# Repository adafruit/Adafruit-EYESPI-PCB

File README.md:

## Adafruit EYESPI Breakout Board PCB

<a href="http://www.adafruit.com/products/5613"><br/>
Click here to purchase one from the Adafruit shop</a>

PCB files for the Adafruit EYESPI Breakout Board. 

Format is EagleCAD schematic and board layout
* https://www.adafruit.com/product/5613

### Description

Our most recent display breakouts have come with a new feature: an 18-pin "EYE SPI" standard FPC connector with flip-top connector. This is intended to be a sort-of "STEMMA QT for displays" - a way to quickly connect and extend display wiring that uses a lot of SPI pins. In this case we need a lot of SPI pins, and we want to be able to use long distances so we go with an 18-pin 0.5mm pitch FPC.

Now you can connect to the displays, but what goes on the other side of the FPC? Here is one possibility - a simple breakout board that brings all the GPIO to 0.1" spaced header, for breadboarding usage. Each pin usage is labeled, and for most display purposes you only need the left half of the display for power and SPI connectivity.

Don't forget you'll also want an 18-pin EYESPI FPC cable.

### License

Adafruit invests time and resources providing this open source design, please support Adafruit and open-source hardware by purchasing products from [Adafruit](https://www.adafruit.com)!

Designed by Limor Fried/Ladyada for Adafruit Industries.

Creative Commons Attribution/Share-Alike, all text above must be included in any redistribution. 
See license.txt for additional details.

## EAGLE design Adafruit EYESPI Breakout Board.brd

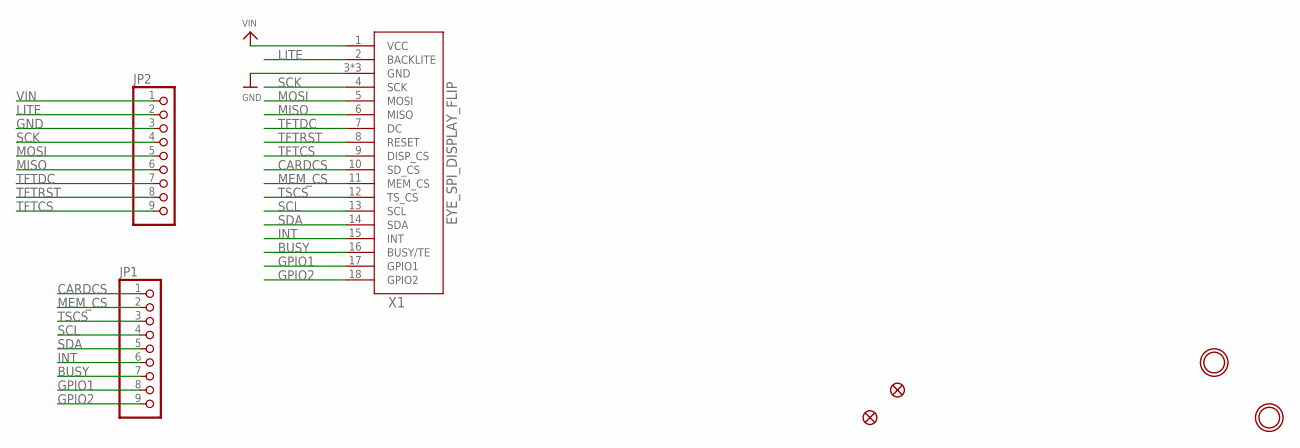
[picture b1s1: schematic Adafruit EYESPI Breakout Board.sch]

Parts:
JP1, JP2: HEADER-1X970MIL; 1X09_ROUND_70
U$4, U$5: FIDUCIAL_1MM
U$9, U$10: MOUNTINGHOLE2.5; MOUNTINGHOLE_2.5_PLATED
X1: EYE_SPI_DISPLAY_FLIP; EYE_SPI_DISPLAY_BOTCONTACT

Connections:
BUSY: JP1.7, X1.16 (BUSY/TE)
CARDCS: JP1.1, X1.10 (SD_CS)
GND: JP2.3, X1.3 (GND), X1.SUPPORT1 (GND), X1.SUPPORT2 (GND)
GPIO1: JP1.8, X1.17 (GPIO1)
GPIO2: JP1.9, X1.18 (GPIO2)
INT: JP1.6, X1.15 (INT)
LITE: JP2.2, X1.2 (BACKLITE)
MEM_CS: JP1.2, X1.11 (MEM_CS)
MISO: JP2.6, X1.6 (MISO)
MOSI: JP2.5, X1.5 (MOSI)
SCK: JP2.4, X1.4 (SCK)
SCL: JP1.4, X1.13 (SCL)
SDA: JP1.5, X1.14 (SDA)
TFTCS: JP2.9, X1.9 (DISP_CS)
TFTDC: JP2.7, X1.7 (DC)
TFTRST: JP2.8, X1.8 (RESET)
TSCS: JP1.3, X1.12 (TS_CS)
VIN: JP2.1, X1.1 (VCC)

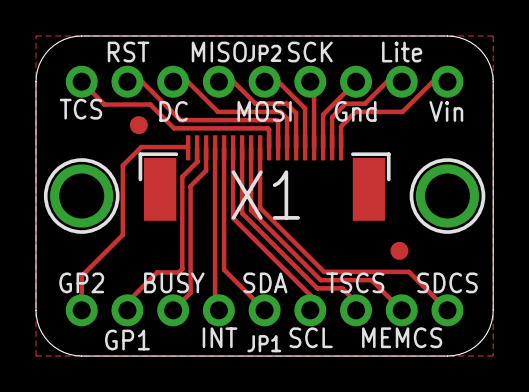
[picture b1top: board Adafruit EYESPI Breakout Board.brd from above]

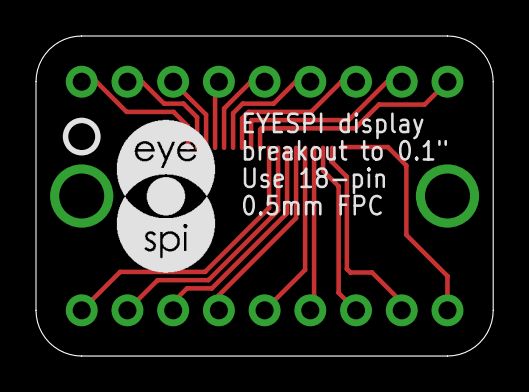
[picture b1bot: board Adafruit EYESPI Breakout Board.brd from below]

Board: 2 copper layers, 25.4 x 17.8 mm, 9 parts (2 on the bottom side), 18 nets.

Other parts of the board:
U$2: PCBFEAT-REV-040
U$22: EYESPI_MINI_LOGO

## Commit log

2022-09-19 Add board files.

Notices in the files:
parts and their libraries:
microbuilder: This work is placed in the public domain, and may be freely used for commercial and non-commercial work with the following conditions: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
